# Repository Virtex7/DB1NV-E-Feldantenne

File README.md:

# DB1NV-E-Feldantenne
JFET-Input Vorverstärker für eine E-Feldsonde, bzw. Antenne für 10kHz bis ca 10MHz

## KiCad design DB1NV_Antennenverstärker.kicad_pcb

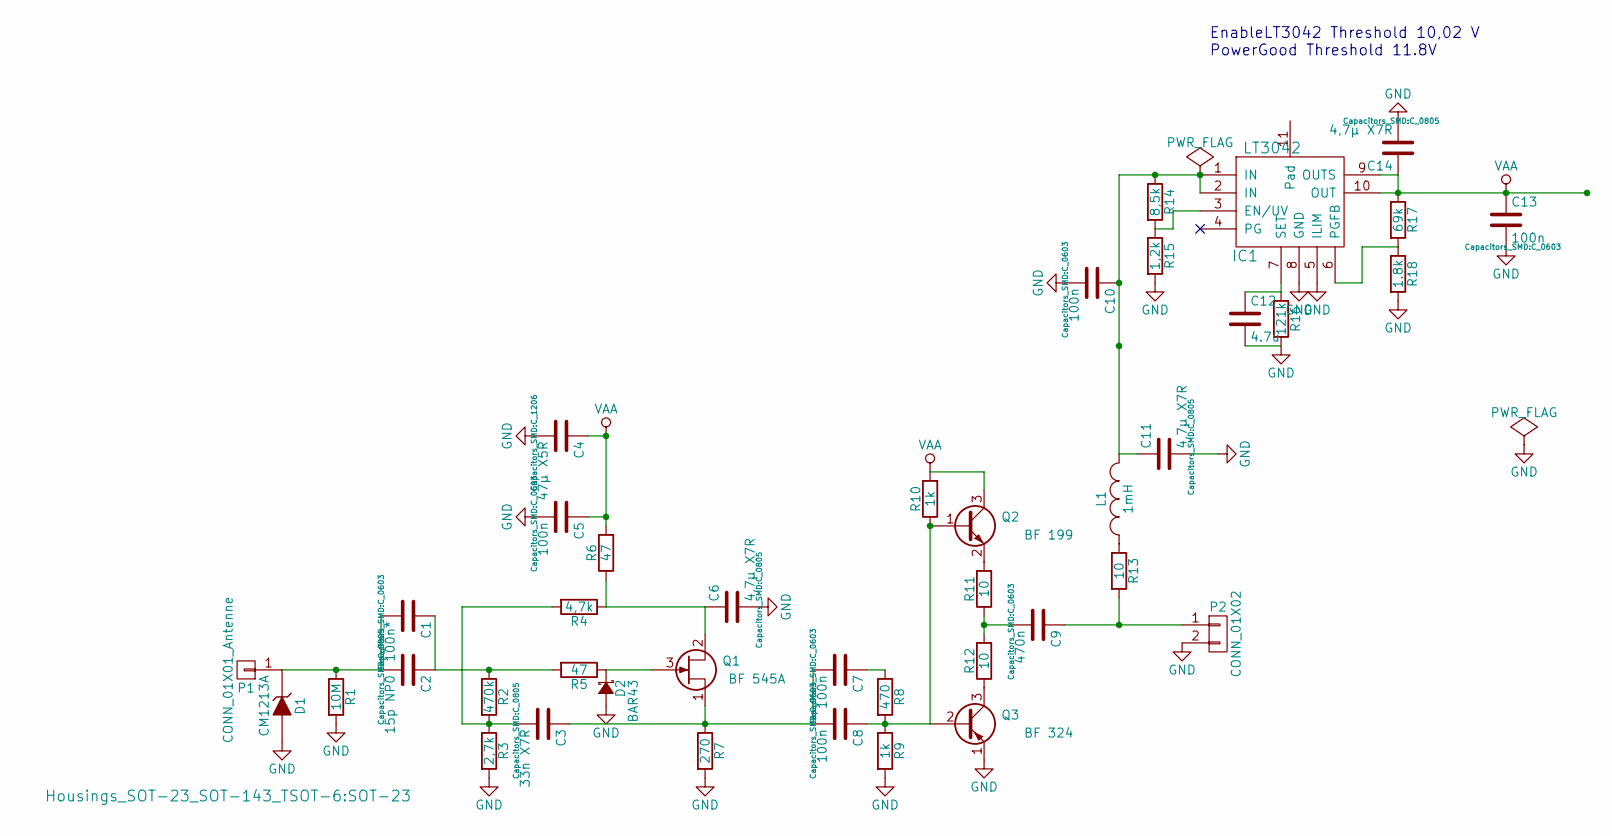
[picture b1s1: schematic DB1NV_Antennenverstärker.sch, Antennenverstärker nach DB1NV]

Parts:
C1: 100n*; C_0603
C2: 15p NP0; C_0805
C3: 33n X7R; C_0805
C4: 47µ X5R; C_1206
C5, C7, C8, C10, C13: 100n; C_0603
C6, C11, C14: 4,7µ X7R; C_0805
C9: 470n; C_0603
C12: 4.7u
D1: CM1213A; SOT-23
D2: BAR43; SOT-23
IC1: LT3042
L1: 1mH; L-PIS2812
P1: CONN_01X01_Antenne; Pin_Header_Straight_1x01
P2: CONN_01X02; Pin_Header_Straight_1x02
Q1: BF 545A; SOT-23
Q2: BF 199; TO-92_Inline_Narrow_Oval
Q3: BF 324; TO-92_Inline_Narrow_Oval
R1: 10M; R_0805
R2: 470k; R_0603
R3: 2,7k; R_0603
R4: 4,7k; R_0603
R5, R6: 47; R_0603
R7: 270; R_0603
R8: 470; R_0603
R9, R10: 1k; R_0603
R11, R12: 10; R_0603
R13: 10; R_0805
R14: 8,5k
R15: 1,2k
R16: 121k
R17: 69k
R18: 1.8k

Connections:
GND: C4.2, C5.2, C6.2, C10.2, C11.2, C12.2, C13.2, C14.2, D1.2 (A), D2.2 (A), IC1.5 (ILIM), IC1.8 (GND), IC1.11 (Pad), P2.2, Q3.1 (E), R1.2, R3.2, R7.2, R9.2, R15.2, R16.2, R18.2
unnamed: C1.1, C2.1, R2.1, R5.2
unnamed: C1.2, C2.2, D1.1 (K), P1.1, R1.1
unnamed: C3.1, C7.2, C8.2, Q1.1 (S), R7.1
unnamed: C3.2, R2.2, R3.1, R4.2
unnamed: C6.1, Q1.2 (D), R4.1, R6.1
unnamed: C7.1, R8.1
unnamed: C8.1, Q2.1 (B), Q3.2 (B), R8.2, R9.1, R10.1
unnamed: C9.1, P2.1, R13.2
unnamed: C9.2, R11.1, R12.2
unnamed: C10.1, C11.1, IC1.1 (IN), IC1.2 (IN), L1.2, R14.1
unnamed: C12.1, IC1.7 (SET), R16.1
unnamed: D2.1 (K), Q1.3 (G), R5.1
unnamed: IC1.3 (EN/UV), R14.2, R15.1
unnamed: IC1.6 (PGFB), R17.2, R18.1
unnamed: L1.1, R13.1
unnamed: Q2.2 (E), R11.2
unnamed: Q3.3 (C), R12.1
VAA: C4.1, C5.1, C13.1, C14.1, IC1.9 (OUTS), IC1.10 (OUT), Q2.3 (C), R6.2, R10.2, R17.1

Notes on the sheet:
EnableLT3042 Threshold 10,02 V PowerGood Threshold 11.8V

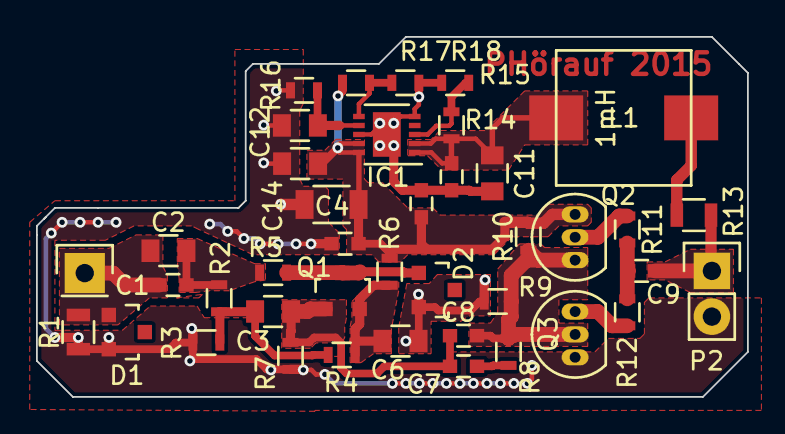
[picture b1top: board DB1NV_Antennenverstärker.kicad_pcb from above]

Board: 2 copper layers, 39.5 x 20.0 mm, 41 parts (0 on the bottom side), 19 nets.

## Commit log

2015-06-19 gitignore eingebaut!
2015-06-19 Platine v0.1 zum E-Feld Empfänger fertiggestellt.
2015-06-26 Hinzufügen des Schaltplansymbols für LT3024
2015-06-26 Hinzufügen des LT3042 zum Schaltplan (Werte der externen Beschaltung noch nicht berechnet)
2015-06-26 Hinzufügen der 3,5mm Klinke LUM1503 (Reichelt)
2015-06-27 Anpassung der Werte des LT3042 Optimierung für Minimales Rauschen (längeres Startup) Undervoltage Threshold = 10.02 V Power Good Threshold = 11.8 V
2015-06-27 Schaltplan leicht modifiziert. eine Spule weniger
2015-08-31 gefertigte Version...
